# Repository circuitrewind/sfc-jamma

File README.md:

# sfc-jamma

TLDR: SNES/SFC controller support on arcade machines!

[Click here for a demo video of a Capcom CP Solder used to play Street Fighter Zero 3](https://www.tiktok.com/@vincerants/video/7230315835842170155)

This repository contains the Eagle CAD files as well as the Arduino Nano source code to interface a Super Famicom (SFC) or Super Nintendo (SNES) controller with an Arcade Cabinet JAMMA interface via a 40-pin ribbon cable.

The 40-pin ribbon cable pinout is based on the pinout used by the [EZ Switchers by RiddledTV](https://riddledtv.com/arcade/ez.html). The EZ 4-way Switcher and EZ 8-way Switcher provide both a JAMMA edge and 40-pin output connectors with the intent of having two cabinets wired into the same arcade board for head-to-head gameplay. I abused this fact to instead use the 40-pin cable for a secondary set of user input controls.

Because the wiring on the JAMMA interface and 40-pin interface are tied directly together, the Arduino Nano can also read input from the arcade's input panel, and then forward this information over the Arduino Nano's USB interface back to a PC, such as using it for gamepad emulation. This can be useful for running a PC through an arcade cabinet, and forwarding the input controls from the cabinet back into the PC.

## Button Mappings
On Player 1, hold SELECT + START for two seconds to toggle TEST / SETTINGS button. This is set as a toggle rather than a momentary press because some games like Soul Edge require the button to remain held while in the settings menu.

On Player 2, hold SELECT + START for two seconds to toggle TILT button. P1 and P2 Arduino Nanos run on the same code, which is why this is also a held toggle function.

Press SELECT + UP to select Profile 1
Press SELECT + DOWN to select Profile 2

|SNES|NES|Profile 1|Profile 2|
|---|---|---|---|
|SELECT|SELECT|Insert Coin|Insert Coin|
|START|START|Player Start|Player Start|
|A||Button 5 (MK)|Button 6 (HK)|
|B|A|Button 4 (LK)|Button 4 (LK)|
|X||Button 2 (MP)|Button 3 (HP)|
|Y|B|Button 1 (LP)|Button 1 (LP)|
|L||Button 3 (HP)|Button 2 (MP)|
|R||Button 6 (HK)|Button 5 (MK)|

## Tested SNES Controllers
* Nintendo Super NES Controller: SNS-005
* Nintendo Super Famicom Controller: SHVC-005
* Nintendo Super NES Score Master: SNSP-026
* NTT Data Key Pad: NDK10 (1)
* Brook Gaming Wingman SNES Converter: ZPP005Q
* 8BitDo Retro Receiver for SNES
* Capcom CP Soldier: CP-S01CAN
* HORI Fatal Fury 2 Commander Controller: HSG-07
* HORI Fighting Commander: HSJ-14
* Hudson Soft Super Joycard: HC-691
* Asciiware AsciiPad: AS-131-SP
* Asciiware Super Advantage: 4910
* Asciiware Fight Stick: AS-9981-SF
* STD SN ProPad: SV-334
* STD SN ProgramPad: SV-337
* Triax Turbo Touch 360
* Tyco Super NES Power Plug: 1286
* Konami Hissatsu Command Controller: RU-009
* High Frequency Clear Turbo Controller for SNES
* FC2 Slim
* Hyperkin Retron 2 Controller: M05932

(1) The NTT Data Key Pad will always have bit 14 pressed (outside of the normal buttons). The four high bits are used to identify the type of device plugged into a controller port, with value 0h being a normal controller. This has a value of 2h, and it most likely used by the accompanying hardware to identify itself and tell the software to do extra querying on the controller to read its additional buttons.

## Tested NES Controllers
* Nintendo Controller: NES-004
* Nintendo NES MAX: NES-027
* 8BitDo N30 2.4g Wireless Gamepad: 81BC
* Brook Gaming Wingman SNES Converter: ZPP005Q

## Images

## vJoy IBUS PC Access
To use this board with a PC, allowing SNES/SFC or JAMMA input as a PC gamepad, you'll need a couple of utilities installed and configured on your PC.
* [vJoy](https://sourceforge.net/projects/vjoystick/)
* [vJoySerialFeeder](https://github.com/Cleric-K/vJoySerialFeeder/releases)
* [Video of JAMMA to PC with Street Fighter 6](https://www.tiktok.com/@vincerants/video/7229858727111888174)

### vJoy Configuration
* Download and install [vJoy](https://sourceforge.net/projects/vjoystick/)
* Make sure that "Enable vJoy" is selected
* Uncheck all but "X" and "Y" from Axes
* Set the number of buttons to 16
* Set "POVs" to "0" in the "POV Hat Switch" panel
* Unchecked "Enable Effects" in the "Force Feedback" panel
* Click the "Apply" button

### vJoySerialFeeder Configuration
* Download and run [vJoySerialFeeder](https://github.com/Cleric-K/vJoySerialFeeder/releases)
* Set "Virtual Joystick" to "vJoy.1"
* Set "Protocol" to "IBUS"
* Click the "Setup" button next to "IBUS" and enable "Use 16-bit channels (Arduino)"
* Set "Port" to the COM port your Arduino Nano is registering to on your PC
* Click "Add Bit-mapped Button" once and "Add Axis" twice to add the three channels this board provides
* Set the "Bits" channel to "1", and configure the individual buttons as: 1, 3, 7, 8, nc, nc, nc, nc, 2, 4, 5, 6, nc, nc, nc, nc
* Set the axis channels to 2 for X, and 3 for Y
* In each axis channel, click their "Setup" button and set: Minimum=0, Center=32768, Maximum=65535
* Once everything is configured click on the "Connect" button to activate the interface

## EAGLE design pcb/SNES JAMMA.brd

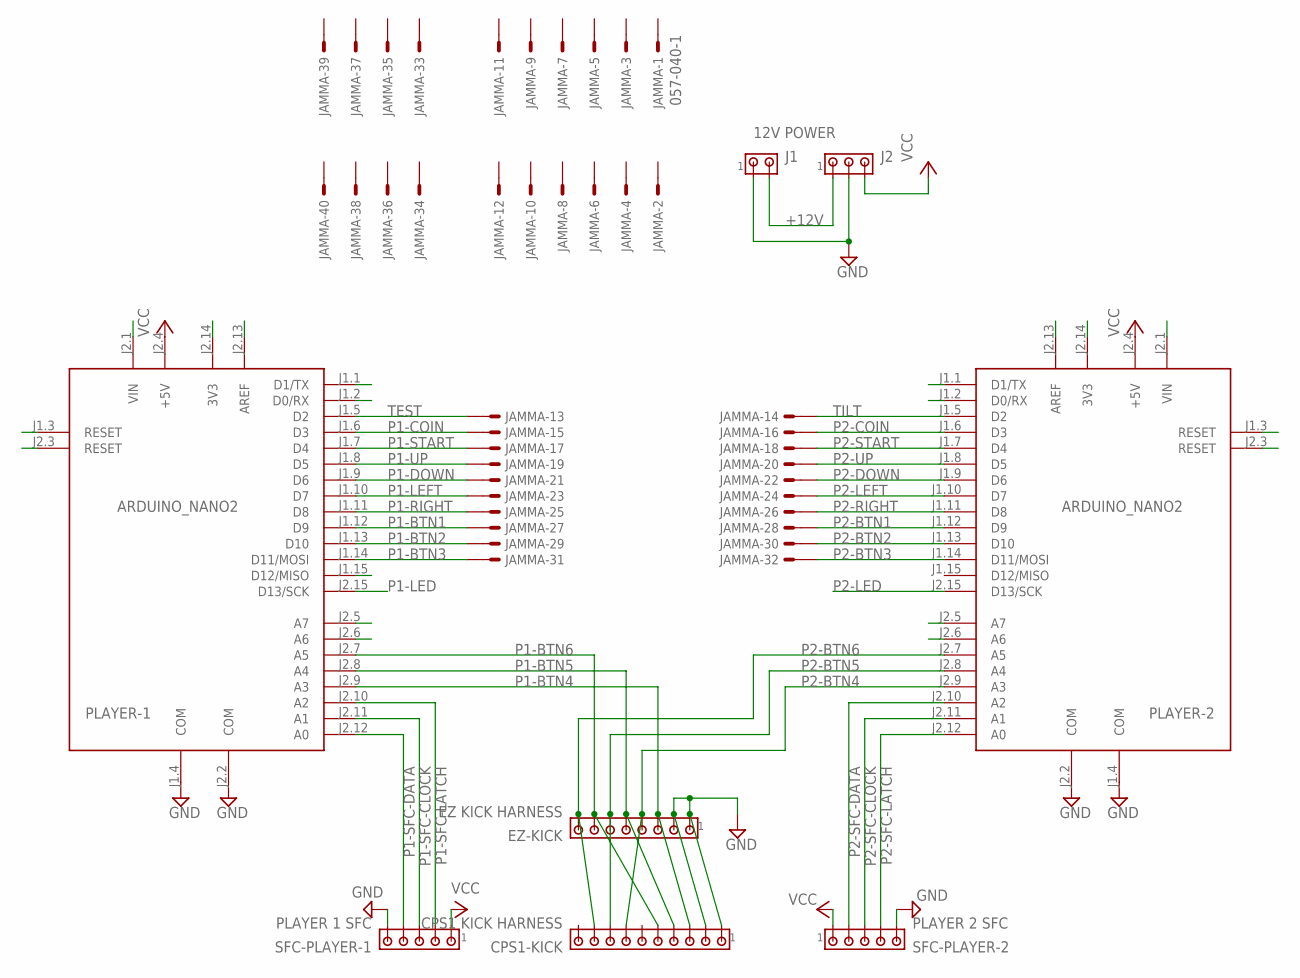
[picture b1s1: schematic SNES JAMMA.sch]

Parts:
CPS1-KICK: CPS1 KICK HARNESS; 10X10MTA
EZ-KICK: EZ KICK HARNESS; 10X08MTA
J1: 12V POWER; 10X02MTA
J2: MTA03-100; 10X03MTA
JAMMA: 057-040-1
PLAYER-1, PLAYER-2: ARDUINO_NANO2
SFC-PLAYER-1: PLAYER 1 SFC; 10X05MTA
SFC-PLAYER-2: PLAYER 2 SFC; 10X05MTA

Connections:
+12V: J1.2, J2.1
GND: CPS1-KICK.1, CPS1-KICK.2, EZ-KICK.1, EZ-KICK.2, J1.1, J2.2, PLAYER-1.J1.4 (COM), PLAYER-1.J2.2 (COM), PLAYER-2.J1.4 (COM), PLAYER-2.J2.2 (COM), SFC-PLAYER-1.5, SFC-PLAYER-2.5
P1-BTN1: JAMMA.27, PLAYER-1.J1.12 (D9)
P1-BTN2: JAMMA.29, PLAYER-1.J1.13 (D10)
P1-BTN3: JAMMA.31, PLAYER-1.J1.14 (D11/MOSI)
P1-BTN4: CPS1-KICK.3, EZ-KICK.3, PLAYER-1.J2.9 (A3)
P1-BTN5: CPS1-KICK.4, EZ-KICK.5, PLAYER-1.J2.8 (A4)
P1-BTN6: CPS1-KICK.5, EZ-KICK.7, PLAYER-1.J2.7 (A5)
P1-COIN: JAMMA.15, PLAYER-1.J1.6 (D3)
P1-DOWN: JAMMA.21, PLAYER-1.J1.9 (D6)
P1-LED: PLAYER-1.J2.15 (D13/SCK)
P1-LEFT: JAMMA.23, PLAYER-1.J1.10 (D7)
P1-RIGHT: JAMMA.25, PLAYER-1.J1.11 (D8)
P1-SFC-CLOCK: PLAYER-1.J2.11 (A1), SFC-PLAYER-1.3
P1-SFC-DATA: PLAYER-1.J2.12 (A0), SFC-PLAYER-1.4
P1-SFC-LATCH: PLAYER-1.J2.10 (A2), SFC-PLAYER-1.2
P1-START: JAMMA.17, PLAYER-1.J1.7 (D4)
P1-UP: JAMMA.19, PLAYER-1.J1.8 (D5)
P2-BTN1: JAMMA.28, PLAYER-2.J1.12 (D9)
P2-BTN2: JAMMA.30, PLAYER-2.J1.13 (D10)
P2-BTN3: JAMMA.32, PLAYER-2.J1.14 (D11/MOSI)
P2-BTN4: CPS1-KICK.7, EZ-KICK.4, PLAYER-2.J2.9 (A3)
P2-BTN5: CPS1-KICK.8, EZ-KICK.6, PLAYER-2.J2.8 (A4)
P2-BTN6: CPS1-KICK.9, EZ-KICK.8, PLAYER-2.J2.7 (A5)
P2-COIN: JAMMA.16, PLAYER-2.J1.6 (D3)
P2-DOWN: JAMMA.22, PLAYER-2.J1.9 (D6)
P2-LED: PLAYER-2.J2.15 (D13/SCK)
P2-LEFT: JAMMA.24, PLAYER-2.J1.10 (D7)
P2-RIGHT: JAMMA.26, PLAYER-2.J1.11 (D8)
P2-SFC-CLOCK: PLAYER-2.J2.11 (A1), SFC-PLAYER-2.3
P2-SFC-DATA: PLAYER-2.J2.12 (A0), SFC-PLAYER-2.4
P2-SFC-LATCH: PLAYER-2.J2.10 (A2), SFC-PLAYER-2.2
P2-START: JAMMA.18, PLAYER-2.J1.7 (D4)
P2-UP: JAMMA.20, PLAYER-2.J1.8 (D5)
TEST: JAMMA.13, PLAYER-1.J1.5 (D2)
TILT: JAMMA.14, PLAYER-2.J1.5 (D2)
VCC: J2.3, PLAYER-1.J2.4 (+5V), PLAYER-2.J2.4 (+5V), SFC-PLAYER-1.1, SFC-PLAYER-2.1

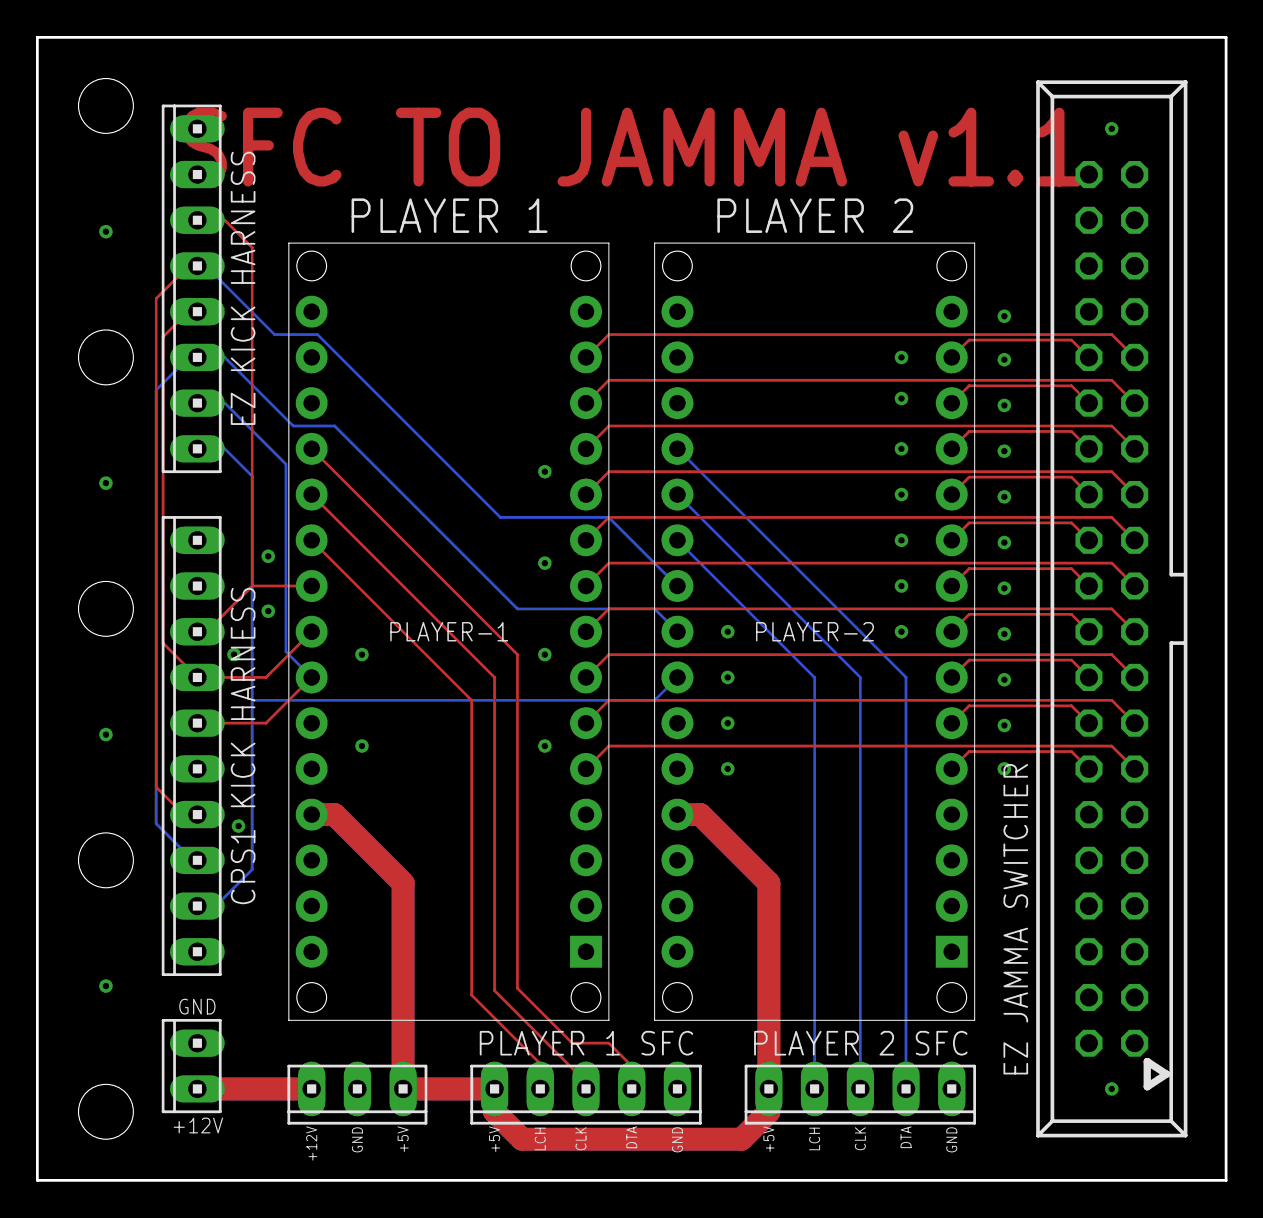
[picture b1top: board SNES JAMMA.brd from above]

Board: 2 copper layers, 66.0 x 63.5 mm, 9 parts (0 on the bottom side), 35 nets.

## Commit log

2023-03-23 Adding PCB files
2023-03-23 Adding Arduino code (flash this to both P1 and P2, they're identical)
2023-05-05 SCF to JAMMA v1.0
2023-05-05 v1.0 PCB and Schematics files
2023-05-05 README.md everythings!
2023-05-05 Minor edits to README.md
2023-05-06 Experimental IBUS addition to firmware NOTE: this will change soon, I want to break out directionals and change button mappings, and recombine SFC and JAMMA inputs on IBUS (probably as 3 separate cha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
2023-05-07 Adding axis reporting for ibus
2023-05-07 Board feels stable now, so removing debug ibus channels Adding JAMMA arcade stick to ibus dpad inputs
2023-05-07 Updating board design to v1.1 Adding ability for P1 Arduino to trigger "test" switch
2023-05-07 Use consistent delays regardless of computational complexity And lots of general code cleanup!
2023-05-07 Listing tested SNES/SFC and compatible controllers
2023-05-08 Adding ability to swap between JAMMA button mapping profiles
2023-05-08 Adding in board revision v1.1 support: TEST MODE BUTTON!
    NOTE: toggle test button/switch by holding START+SELECT for 2 seconds. This is a toggle rather than a momentary press because games like Soul Edge require the button to be held down to remain in the 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
    Other than adding more button mappings in the future, this will probably be the final firmware revision
2023-05-08 Forgot a comment line. Doesn't effect compiled firmware tho :P
2023-05-08 Adding more images
2023-05-08 WHOOPSIES purchased another SNES controller today from Pink Gorilla Games in Seattle! :D
2023-05-08 Adding button mapping info to the README.md file
2023-05-08 Correcting P1 TEST toggle incorrectly being wired to TILT instead P1 TEST is now properly TEST toggle Additionally, P2's is now wired into TILT so they're both available to be used!
2023-05-08 Adding in the vJoy configuration instructions to use this board as a JAMMA to PC interface
2023-05-08 LOL whoopsies, fixing file extensions
2023-05-08 Spacing out images
2023-06-23 NES Controller support added
2023-06-23 Adding "FC2 Slim" and "Hyperkin Retron 2 Controller" to tested list
2023-06-23 Adding documentation on NES controller compatibility
2023-06-27 ... typos ...
2023-06-28 Adding testing: Nintendo Super NES Score Master: SNSP-026
2023-07-07 FINALLY got the chance to test the official USA SNES controller! LOLOLOLOLOL
2023-08-01 Remove a 6 microsecond delay inside the SFC controller polling function
2023-08-01 Adding NTT Data Key Pad to the list! This one is interesting ;)
